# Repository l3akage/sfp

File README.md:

# SFP

Tool to read/write SFP informations/firmware

## Install
```bash
go get -u github.com/l3akage/sfp
```

## Usage
```bash
Small Form-factor Pluggable Inter-Integrated Circuit Bus Reader/Writer

Usage:
  sfp [flags]
  sfp [command]

Available Commands:
  crack       Crack SFP password
  dump        Dump firmware
  fixcrc      Fix Checksum
  help        Help about any command
  info        Read SFP
  version     Print the version number of sfp

Flags:
      --debug           Enable debugging messages
      --device string   path to i2c device (default is /dev/i2c-1) (default "/dev/i2c-1")
  -h, --help            help for sfp

Use "sfp [command] --help" for more information about a command.
```

## License
(c) Martin Poppen, 2019. Licensed under [MIT](LICENSE) license.

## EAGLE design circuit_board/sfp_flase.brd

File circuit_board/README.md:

# SFP Shield for Raspberry Pi

With this shield you can read SFP informations and firmware through i2c.

It has LEDs for TX_FAULT and RX_LOS which are also readable via GPIO

# Pins
GPIO     | Description
---------|-------------
4 | RATE_SELECT
17 | TX_DISABLE (set to 0 to turn on laser)
22 | RX_LOS
27 | TX_FAULT

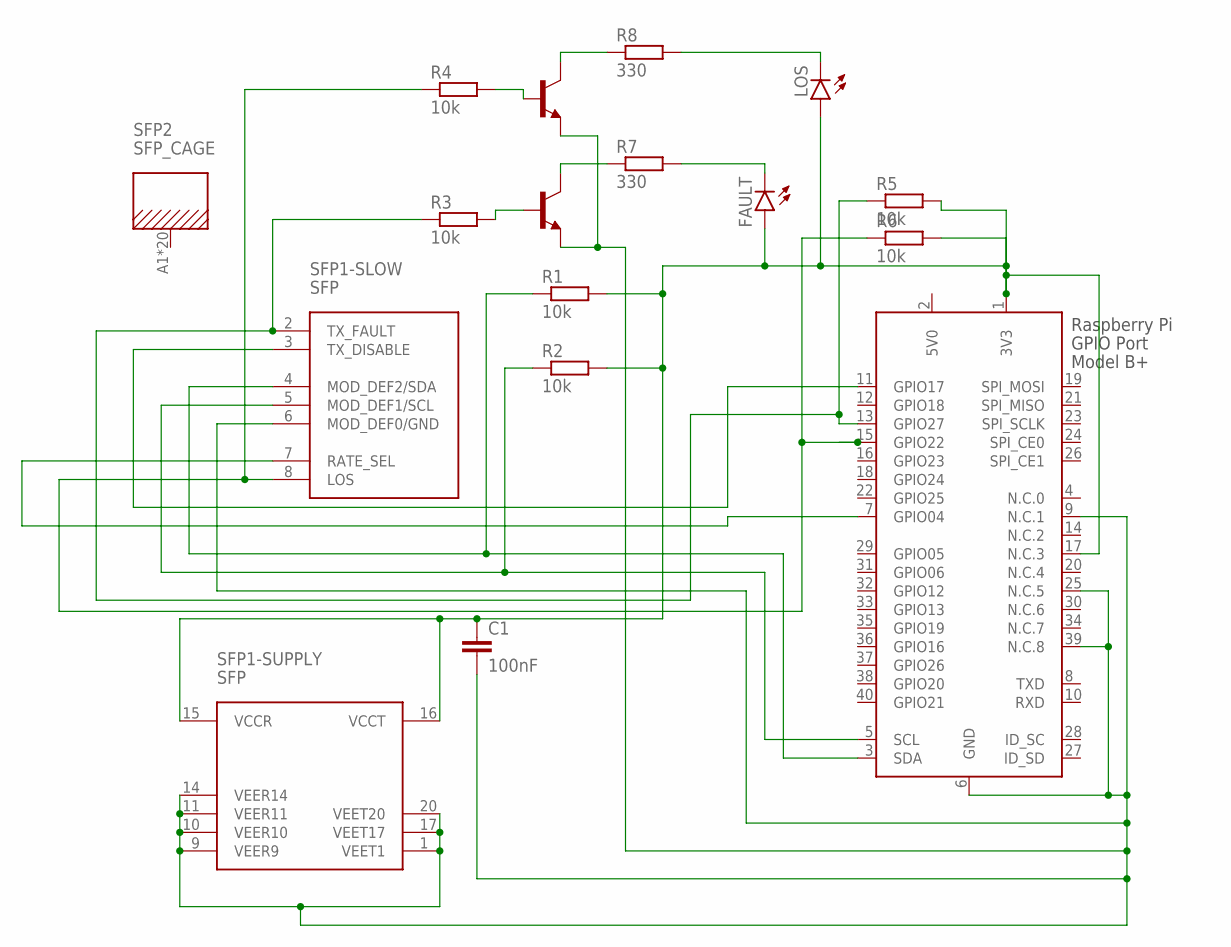
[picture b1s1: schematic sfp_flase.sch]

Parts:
C1: 100nF; C1206
FAULT: LEDCHIPLED_1206; CHIPLED_1206
LOS: LEDCHIPLED_1206; CHIPLED_1206
R1, R2, R3, R4, R5, R6: 10k; M1206
R7, R8: 330; M1206
SFP1: SFP
SFP2: SFP_CAGE
T1, T2: BC847; SOT23
X1: RASPI_BOARD_B+_E0; RASPI_BOARD_B+_EDGES_0DRILL

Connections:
3V3: C1.1, FAULT.A, LOS.A, R1.2, R2.2, R5.2, R6.2, SFP1.15 (VCCR), SFP1.16 (VCCT), X1.1 (3V3), X1.17 (N.C.3)
5V0: X1.2 (5V0)
GND: C1.2, SFP1.1 (VEET1), SFP1.6 (MOD_DEF0/GND), SFP1.9 (VEER9), SFP1.10 (VEER10), SFP1.11 (VEER11), SFP1.14 (VEER14), SFP1.17 (VEET17), SFP1.20 (VEET20), SFP2.A1, SFP2.A2, SFP2.A3, SFP2.A4, SFP2.A5, SFP2.A6, SFP2.A7, SFP2.A8, SFP2.A10, SFP2.A11, SFP2.A12, SFP2.B1, SFP2.B2, SFP2.B3, SFP2.B4, SFP2.B5, SFP2.B6, SFP2.B7, SFP2.B8, SFP2.B10, T1.2 (E), T2.2 (E), X1.6 (GND), X1.9 (N.C.1), X1.25 (N.C.5), X1.39 (N.C.8)
unnamed: R2.1, SFP1.5 (MOD_DEF1/SCL), X1.5 (SCL)
unnamed: R1.1, SFP1.4 (MOD_DEF2/SDA), X1.3 (SDA)
unnamed: R3.1, R5.1, SFP1.2 (TX_FAULT), X1.13 (GPIO27)
unnamed: SFP1.3 (TX_DISABLE), X1.11 (GPIO17)
unnamed: R4.2, T1.1 (B)
unnamed: R3.2, T2.1 (B)
unnamed: R8.1, T1.3 (C)
unnamed: R7.1, T2.3 (C)
unnamed: FAULT.C, R7.2
unnamed: LOS.C, R8.2
unnamed: SFP1.7 (RATE_SEL), X1.7 (GPIO04)
unnamed: R4.1, R6.1, SFP1.8 (LOS), X1.15 (GPIO22)

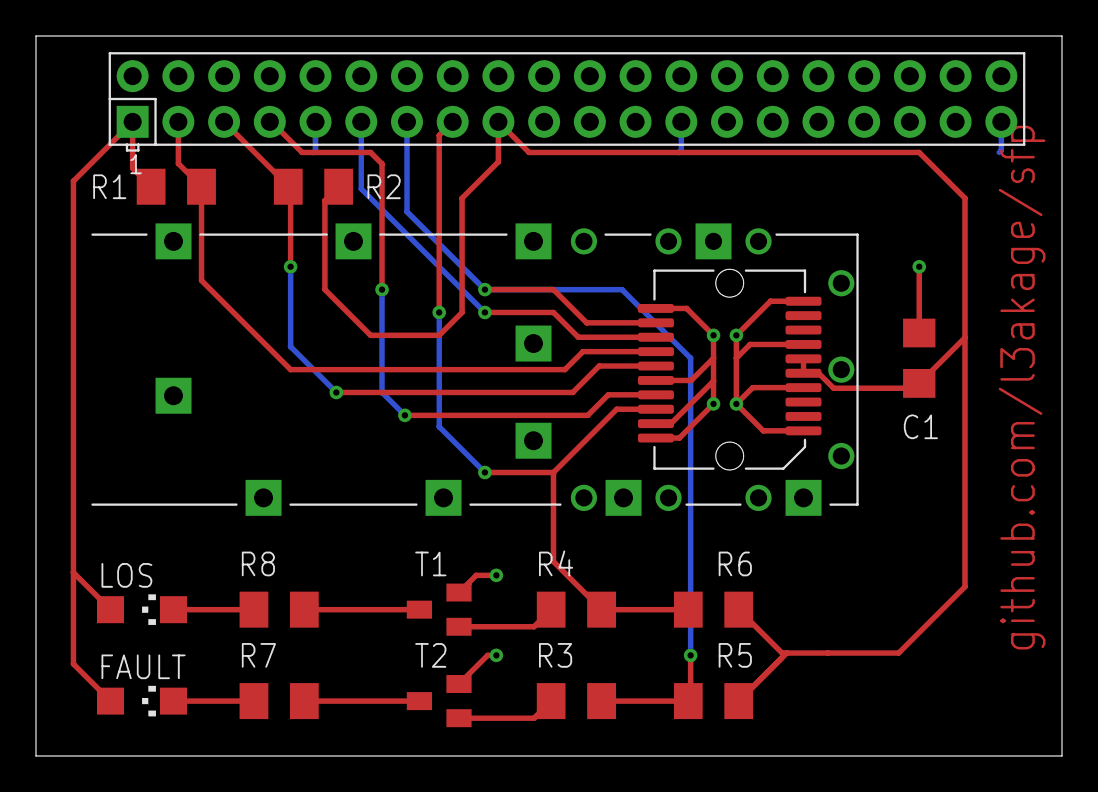
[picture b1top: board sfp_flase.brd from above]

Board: 2 copper layers, 57.0 x 40.0 mm, 16 parts (0 on the bottom side), 14 nets.
